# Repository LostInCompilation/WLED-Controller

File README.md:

# WLED Controller with 4 Channels, line audio input and microphone

<h3 align="center">3D Board view</h3>

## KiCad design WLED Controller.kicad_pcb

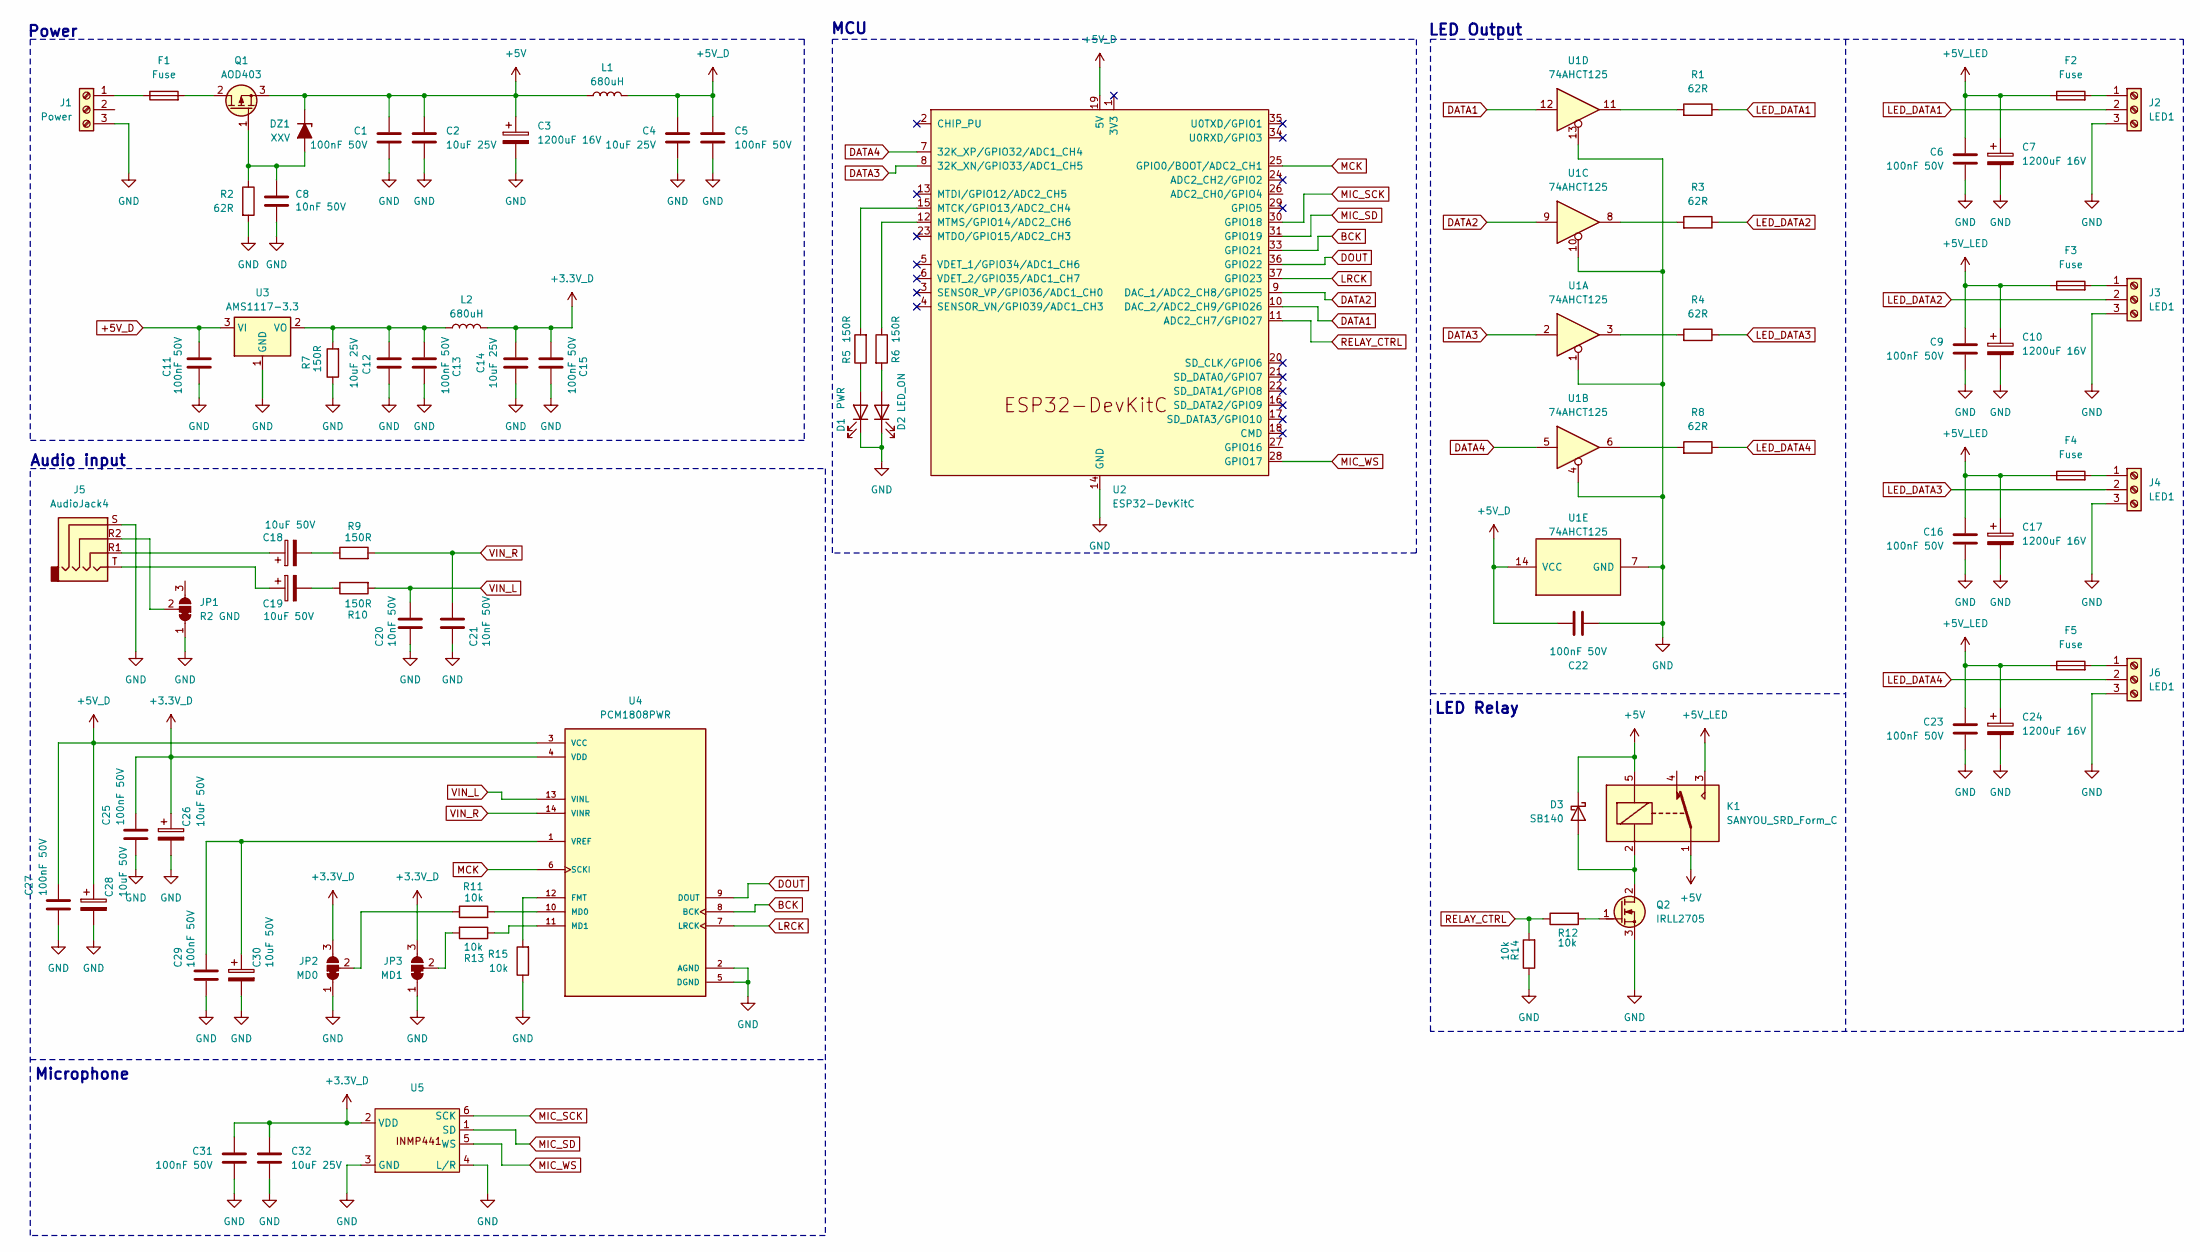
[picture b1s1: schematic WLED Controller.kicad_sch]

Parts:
C1, C5, C6, C9, C11, C13, C15, C16, C22, C23, C25, C27, C29, C31: 100nF 50V; C_1206_3216Metric
C2, C4, C12, C14, C32: 10uF 25V; C_1206_3216Metric
C3, C7, C10, C17, C24: 1200uF 16V; CP_Radial_D10.0mm_P5.00mm
C8, C20, C21: 10nF 50V; C_1206_3216Metric
C18, C19, C26, C28, C30: 10uF 50V; CP_Radial_D5.0mm_P2.50mm
D1: PWR; LED_D3.0mm
D2: LED_ON; LED_D3.0mm
D3: SB140; D_DO-41_SOD81_P10.16mm_Horizontal
DZ1: XXV; D_DO-41_SOD81_P10.16mm_Horizontal
F1, F2, F3, F4, F5: Fuse; Fuseholder_Littelfuse_Nano2_154x
J1: Power; ScrewPlug_3P_Vertical
J2, J3, J4, J6: LED1; ScrewPlug_3P_Vertical
J5: AudioJack4; Jack_3.5mm_PJ320D_Horizontal
JP1: R2 GND; SolderJumper-3_P1.3mm_Bridged12_Pad1.0x1.5mm
JP2: MD0; SolderJumper-3_P1.3mm_Bridged12_Pad1.0x1.5mm
JP3: MD1; SolderJumper-3_P1.3mm_Bridged12_Pad1.0x1.5mm
K1: SANYOU_SRD_Form_C; Relay_SPDT_SANYOU_SRD_Series_Form_C
L1, L2: 680uH; L_10.4x10.4_H4.8
Q1: AOD403; TO-252-2
Q2: IRLL2705; SOT-223-3_TabPin2
R1, R2, R3, R4, R8: 62R; R_Axial_DIN0207_L6.3mm_D2.5mm_P10.16mm_Horizontal
R5, R6, R7, R9, R10: 150R; R_1206_3216Metric
R11, R12, R13, R14, R15: 10k; R_1206_3216Metric
U1: 74AHCT125; TSSOP-14_4.4x5mm_P0.65mm
U2: ESP32-DevKitC
U3: AMS1117-3.3; SOT-223-3_TabPin2
U4: PCM1808PWR; SOP65P640X120-14N; PARTREV B
U5: INMP441_Module

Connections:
+3.3V_D: C14.1, C15.1, C25.1, C26.1, C31.1, C32.1, JP2.3 (B), JP3.3 (B), L2.2, U4.4 (VDD), U5.2 (VDD)
+5V: C1.1, C2.1, C3.1, D3.1 (K), DZ1.1 (K), K1.1, K1.5, L1.1, Q1.3 (S)
+5V_D: C4.1, C5.1, C11.1, C22.2, C27.1, C28.1, L1.2, U1.14 (VCC), U2.19 (5V), U3.3 (VI), U4.3 (VCC)
+5V_LED: C6.1, C7.1, C9.1, C10.1, C16.1, C17.1, C23.1, C24.1, F2.1, F3.1, F4.1, F5.1, K1.3
BCK: U2.33 (GPIO21), U4.8 (BCK)
DATA1: U1.12, U2.10 (DAC_2/ADC2_CH9/GPIO26)
DATA2: U1.9, U2.9 (DAC_1/ADC2_CH8/GPIO25)
DATA3: U1.2, U2.8 (32K_XN/GPIO33/ADC1_CH5)
DATA4: U1.5, U2.7 (32K_XP/GPIO32/ADC1_CH4)
DOUT: U2.36 (GPIO22), U4.9 (DOUT)
GND: C1.2, C2.2, C3.2, C4.2, C5.2, C6.2, C7.2, C8.2, C9.2, C10.2, C11.2, C12.2, C13.2, C14.2, C15.2, C16.2, C17.2, C20.2, C21.2, C22.1, C23.2, C24.2, C25.2, C26.2, C27.2, C28.2, C29.2, C30.2, C31.2, C32.2, D1.1 (K), D2.1 (K), J1.3, J2.3, J3.3, J4.3, J5.S, J6.3, JP1.1 (A), JP2.1 (A), JP3.1 (A), Q2.3 (S), R2.1, R7.2, R14.2, R15.2, U1.1, U1.4, U1.7 (GND), U1.10, U1.13, U2.14 (GND), U2.32 (GND), U2.38 (GND), U3.1 (GND), U4.2 (AGND), U4.5 (DGND), U5.3 (GND), U5.4 (L/R)
LED_DATA1: J2.2, R1.2
LED_DATA2: J3.2, R3.2
LED_DATA3: J4.2, R4.2
LED_DATA4: J6.2, R8.2
LRCK: U2.37 (GPIO23), U4.7 (LRCK)
MCK: U2.25 (GPIO0/BOOT/ADC2_CH1), U4.6 (SCKI)
MIC_SCK: U2.30 (GPIO18), U5.6 (SCK)
MIC_SD: U2.31 (GPIO19), U5.1 (SD)
MIC_WS: U2.28 (GPIO17), U5.5 (WS)
unnamed: C18.1, J5.R1
unnamed: C18.2, R9.2
unnamed: C19.1, J5.T
unnamed: C19.2, R10.2
unnamed: D1.2 (A), R5.2
unnamed: D2.2 (A), R6.1
unnamed: D3.2 (A), K1.2, Q2.2 (D)
unnamed: C8.1, DZ1.2 (A), Q1.1 (G), R2.2
unnamed: F1.1, J1.1
unnamed: F2.2, J2.1
unnamed: F3.2, J3.1
unnamed: F4.2, J4.1
unnamed: F5.2, J6.1
unnamed: J5.R2, JP1.2 (C)
unnamed: JP2.2 (C), R11.2
unnamed: JP3.2 (C), R13.1
unnamed: F1.2, Q1.2 (D)
unnamed: Q2.1 (G), R12.1
unnamed: R1.1, U1.11
unnamed: R3.1, U1.8
unnamed: R4.1, U1.3
unnamed: R8.1, U1.6
unnamed: R5.1, U2.15 (MTCK/GPIO13/ADC2_CH4)
unnamed: R6.2, U2.12 (MTMS/GPIO14/ADC2_CH6)
unnamed: C12.1, C13.1, L2.1, R7.1, U3.2 (VO)
unnamed: R15.1, U4.12 (FMT)
unnamed: R11.1, U4.10 (MD0)
unnamed: R13.2, U4.11 (MD1)
unnamed: C29.1, C30.1, U4.1 (VREF)
RELAY_CTRL: R12.2, R14.1, U2.11 (ADC2_CH7/GPIO27)
VIN_L: C20.1, R10.1, U4.13 (VINL)
VIN_R: C21.1, R9.1, U4.14 (VINR)

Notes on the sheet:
Audio input
Power
LED Relay
Microphone
LED Output
MCU

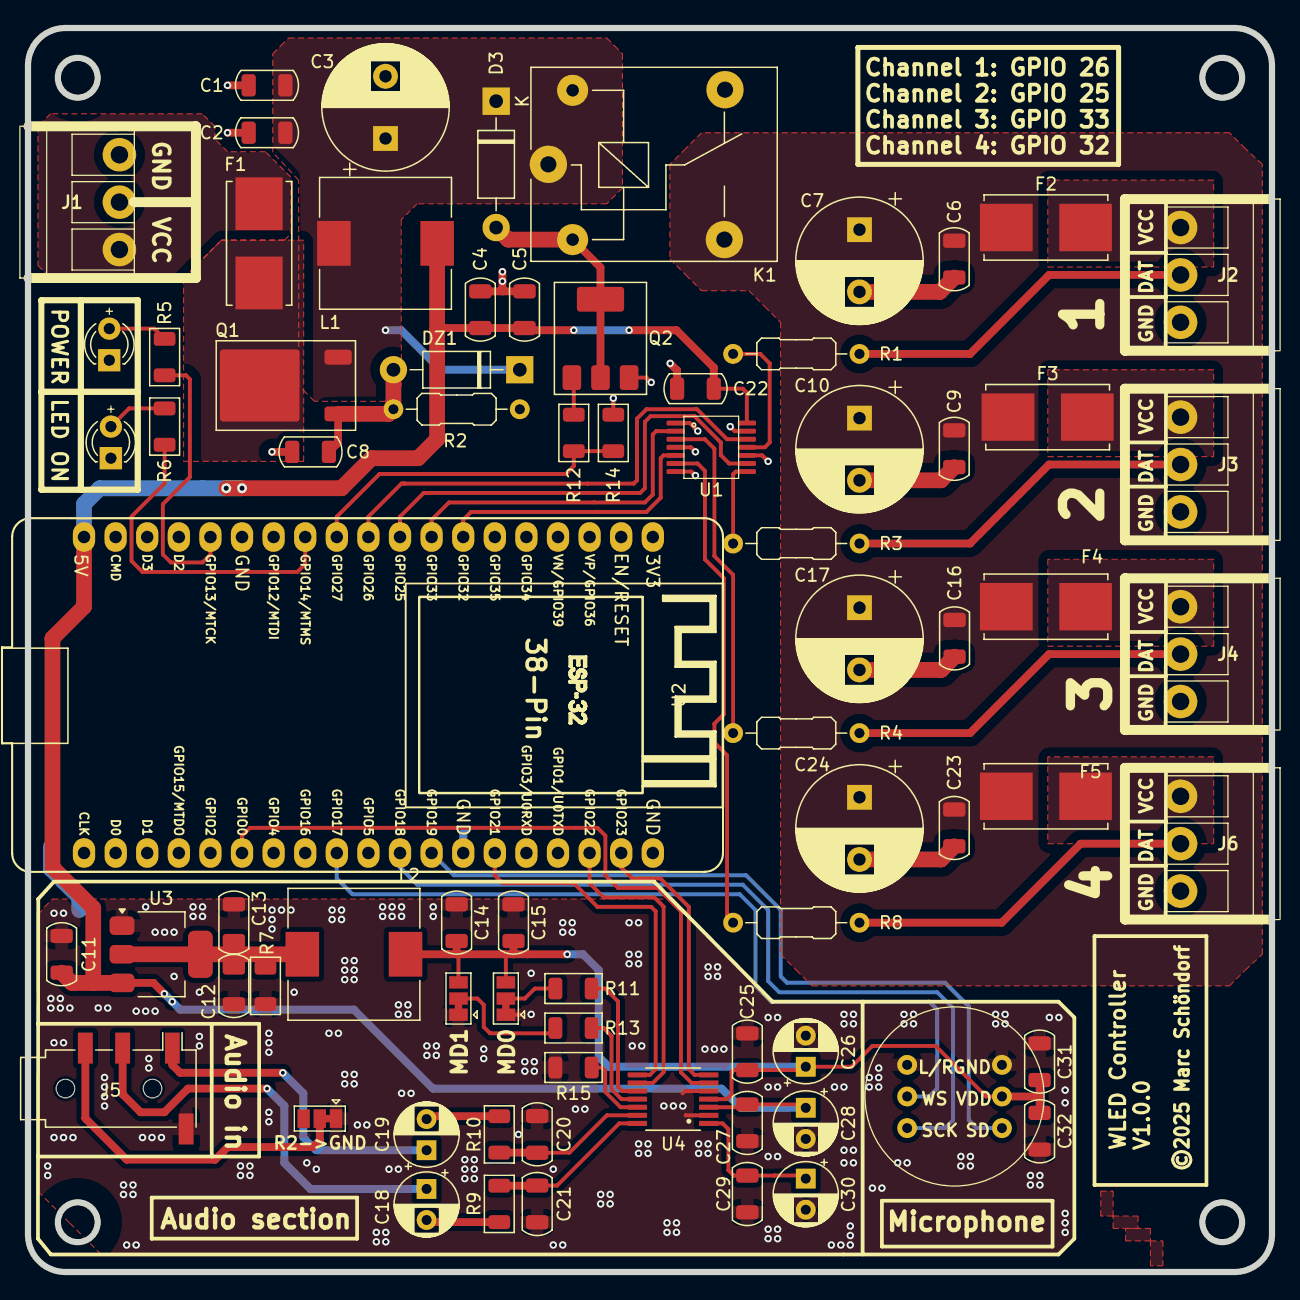
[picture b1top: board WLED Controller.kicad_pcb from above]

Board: 2 copper layers, 100.0 x 100.0 mm, 75 parts (0 on the bottom side), 52 nets.

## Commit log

2025-01-23 Added PDF and BOM.
2025-01-23 Added 3D view.
2025-01-24 Switched to 38pin ESP32 DevKit. Optimizations.
2025-01-24 File renaming
2025-01-24 Silk screen update
2025-01-24 Schematic background
2025-01-24 Switched relay driver to MOSFET. Optimizations.
2025-01-24 Optimizations

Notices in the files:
WLED Controller.kicad_pcb:
(C) 2025 Marc Schöndorf
©2025 Marc Schöndorf
